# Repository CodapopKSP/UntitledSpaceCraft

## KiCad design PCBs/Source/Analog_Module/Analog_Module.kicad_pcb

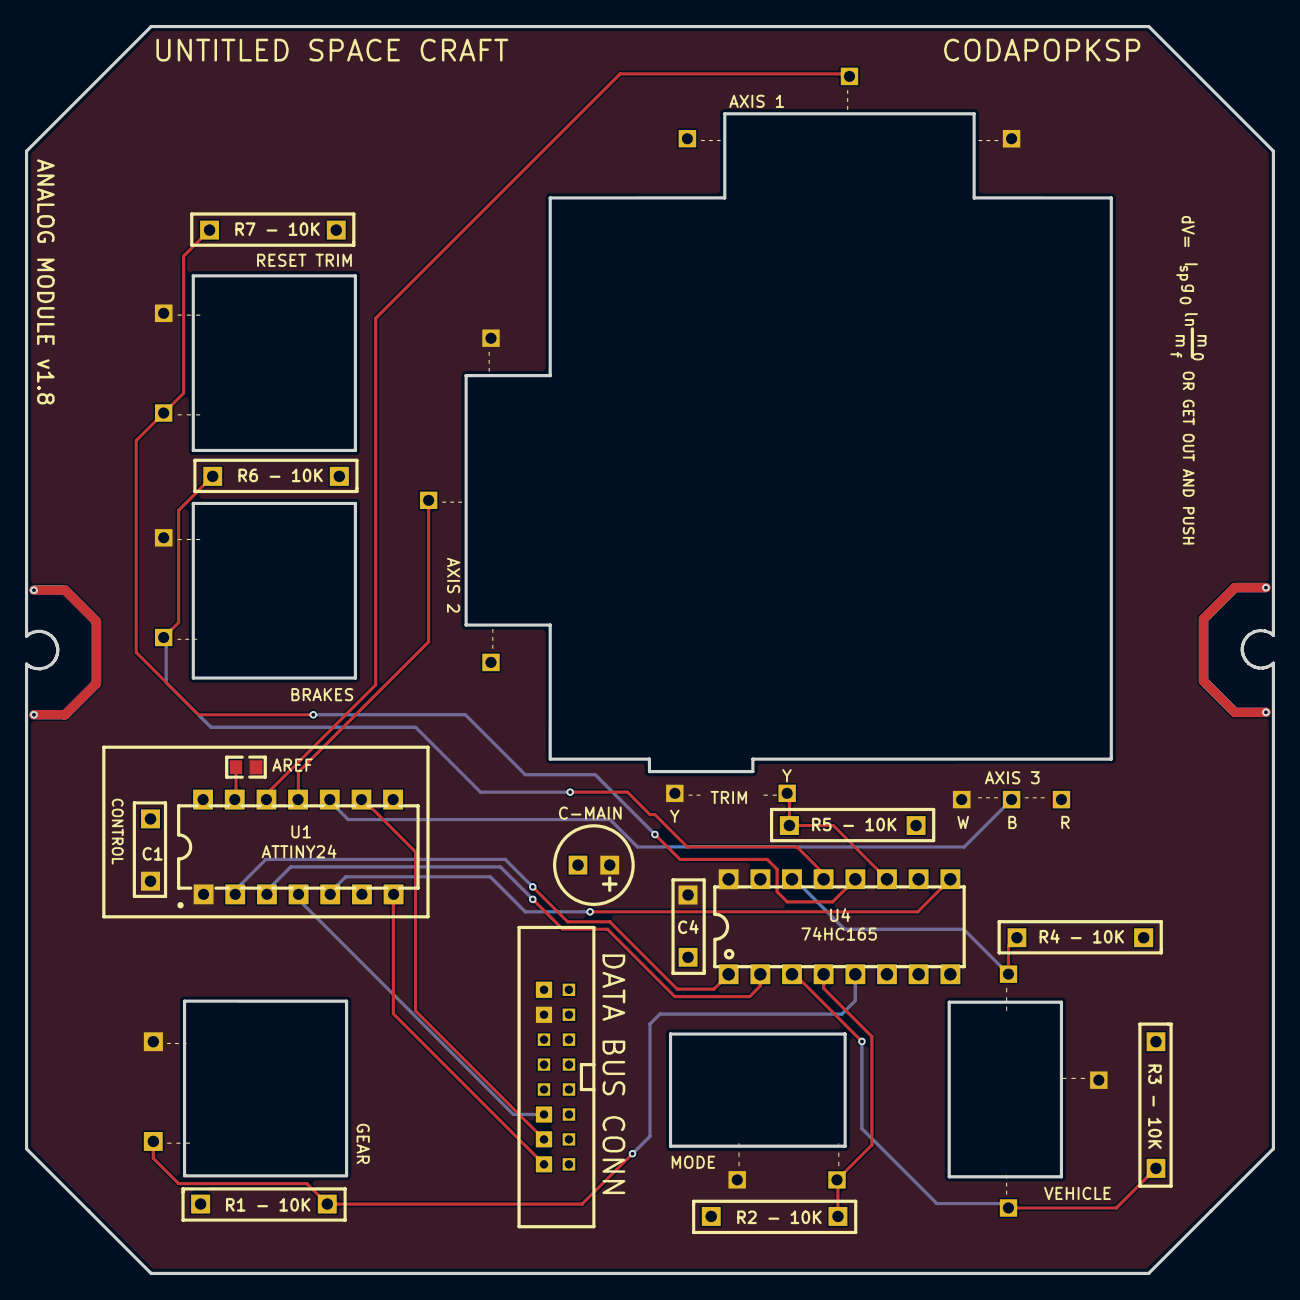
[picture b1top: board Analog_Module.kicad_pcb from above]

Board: 2 copper layers, 100.0 x 100.0 mm, 64 parts (0 on the bottom side), 19 nets.

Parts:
AREF: 10k; R0603
C1, C4: C104; TH_CAP_5mm
C-MAIN: 10uf; CAP-D6.3×F2.5
R1, R2, R3, R4, R5, R6, R7: - 10K; TH_RES_10mm
TP_+5V, TP_+5V#2, TP_+5V#3, TP_+5V#4, TP_+5V#5, TP_+5V#6, TP_+5V#7, TP_+5V#8, TP_+5V#9, TP_+5V#10: WirePad
TP_AREF: WirePad
TP_AXIS1, TP_AXIS1#2, TP_AXIS2, TP_AXIS2#2, TP_AXIS3, TP_AXIS3#2: WirePad
TP_BRAKES: WirePad
TP_CLOCK_Y_: WirePad
TP_CRUISE: WirePad
TP_DATA_P_: WirePad
TP_GEAR: WirePad
TP_GND: WirePad
TP_GND#2, TP_GND#3, TP_GND#4: WirePad
TP_LATCH_G_: WirePad
TP_MODE1, TP_MODE2: WirePad
TP_RESET: WirePad
TP_RESETTRIM: WirePad
TP_SCL: WirePad
TP_SDA: WirePad
TP_THROTTLE: WirePad
TP_TRANS: WirePad
TP_TRIM: WirePad
U4: 74HC165; DIP-16_L20.0-W6.4-P2.54-LS7.6-BL
WP11, WP24, WP25, WP38, WP39, WP43, WP44, WP45, WP46, WP47, WP48, WP49, WP50, WP51, WP52, WP53: WPAD-1-30AWG; WPAD-1-PTH-30AWG

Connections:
+5V: AREF.2, C1.2, C4.2, C-MAIN.1, TP_+5V.1, TP_+5V#2.1, TP_+5V#3.1, TP_+5V#4.1, TP_+5V#5.1, TP_+5V#6.1, TP_+5V#7.1, TP_+5V#8.1, TP_+5V#9.1, TP_+5V#10.1, U4.16, WP46.1
AREF: AREF.1, TP_AREF.13
AXIS1: TP_AXIS1.1, TP_AXIS1#2.12
AXIS2: TP_AXIS2.11, TP_AXIS2#2.1
AXIS3: TP_AXIS3.1, TP_AXIS3#2.10
BRAKES: R6.2, TP_BRAKES.1, U4.13
CLOCK(Y): TP_CLOCK_Y_.3, U4.2
DATA(P): TP_DATA_P_.5, U4.9
GEAR: R1.2, TP_GEAR.1, U4.5
GND: C1.1, C4.1, C-MAIN.2, R1.1, R2.1, R3.1, R4.1, R5.1, R6.1, R7.1, TP_GND.14, TP_GND#2.1, TP_GND#3.1, TP_GND#4.1, U4.6, U4.8, U4.15, WP45.1
LATCH(G): TP_LATCH_G_.2, U4.1
MODE1: R4.2, TP_MODE1.1, U4.14
MODE2: R3.2, TP_MODE2.1, U4.3
RESET: TP_RESET.4, WP50.1
RESETTRIM: R7.2, TP_RESETTRIM.1, U4.12
SCL: TP_SCL.9, WP51.1
SDA: TP_SDA.7, WP52.1
TRANS: R2.2, TP_TRANS.1, U4.4
TRIM: R5.2, TP_TRIM.1, U4.11

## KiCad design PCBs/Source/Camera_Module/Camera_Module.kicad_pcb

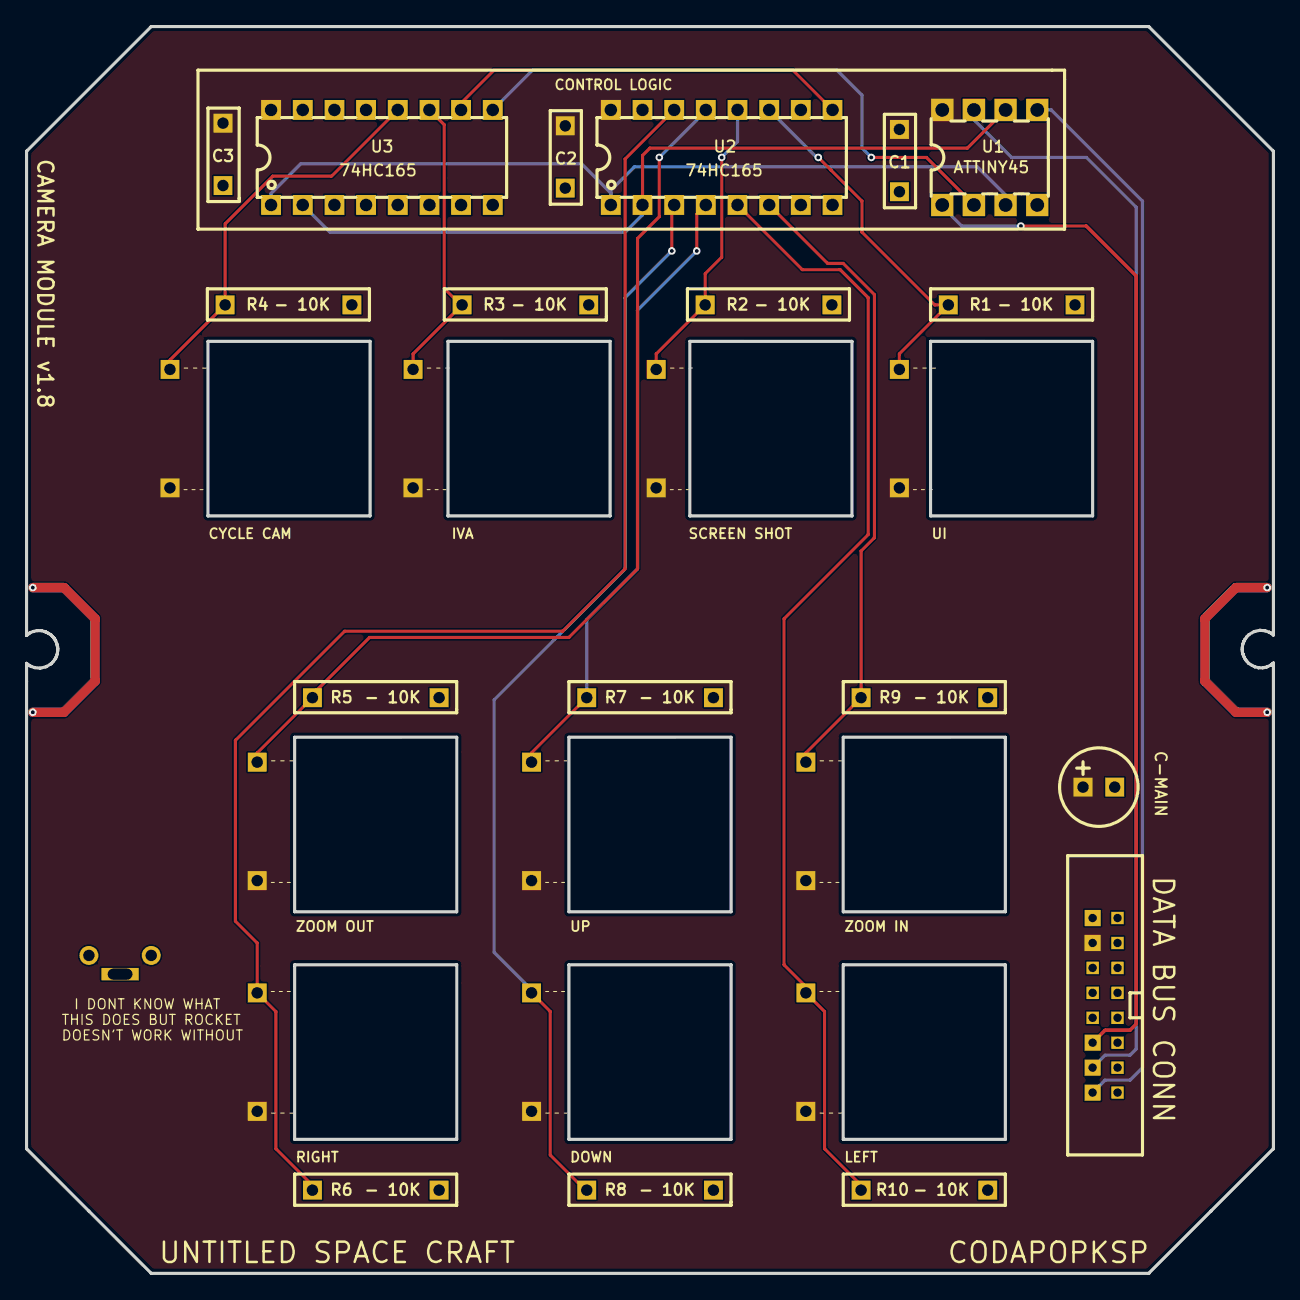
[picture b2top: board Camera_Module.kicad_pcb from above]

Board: 2 copper layers, 100.0 x 100.0 mm, 56 parts (0 on the bottom side), 19 nets.

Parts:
C1, C2, C3: C104; TH_CAP_5mm
C-MAIN: 10uf; CAP-D6.3×F2.5
R1, R2, R3, R4, R5, R6, R7, R8, R9, R10: - 10K; TH_RES_10mm
TP_+5V, TP_+5V#2, TP_+5V#3, TP_+5V#4, TP_+5V#5, TP_+5V#6, TP_+5V#7, TP_+5V#8, TP_+5V#9, TP_+5V#10: WirePad
TP_Pad_gge40554, TP_Pad_gge44183, TP_Pad_gge44204: WirePad
TP_UI1, TP_UI2, TP_UI3, TP_UI4, TP_UI5, TP_UI6, TP_UI7, TP_UI8, TP_UI9, TP_UI10: WirePad
U1: ATtiny45; PDIP-8_L9.3-W6.4-P2.54-LS7.6-BL
U2, U3: 74HC165; DIP-16_L20.0-W6.4-P2.54-LS7.6-BL
WP1, WP2, WP3, WP4, WP5, WP6, WP7, WP8, WP9, WP10, WP11, WP12, WP13, WP14, WP15, WP16: WPAD-1-30AWG; WPAD-1-PTH-30AWG

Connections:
+5V: C1.2, C2.2, C3.2, C-MAIN.1, TP_+5V#2.22, TP_+5V#6.10, TP_+5V#7.12, U1.8, U2.16, U3.16, WP7.1
CLOCK(Y): U1.6, U2.2, U3.2
DATA(B): U2.9, U3.10
DATA(P): U1.2, U3.9
GND: C1.1, C2.1, C3.1, C-MAIN.2, R1.1, R2.1, R3.1, R4.1, R5.1, R6.1, R7.1, R8.1, R9.1, R10.1, U1.4, U2.8, U2.15, U3.3, U3.4, U3.5, U3.6, U3.8, U3.13, U3.14, U3.15, WP8.1
LATCH(G): U1.3, U2.1, U3.1
RESET: U1.1, WP3.1
SCL: U1.7, WP2.1
SDA: U1.5, WP1.1
UI1: R1.2, TP_UI1.9, U2.11
UI2: R2.2, TP_UI2.11, U2.12
UI3: R3.2, TP_UI3.13, U3.11
UI4: R4.2, TP_UI4.15, U3.12
UI5: R5.2, TP_UI5.17, U2.13
UI6: R6.2, TP_UI6.23, U2.14
UI7: R7.2, TP_UI7.19, U2.4
UI8: R8.2, TP_UI8.25, U2.3
UI9: R9.2, TP_UI9.21, U2.6
UI10: R10.2, TP_UI10.27, U2.5

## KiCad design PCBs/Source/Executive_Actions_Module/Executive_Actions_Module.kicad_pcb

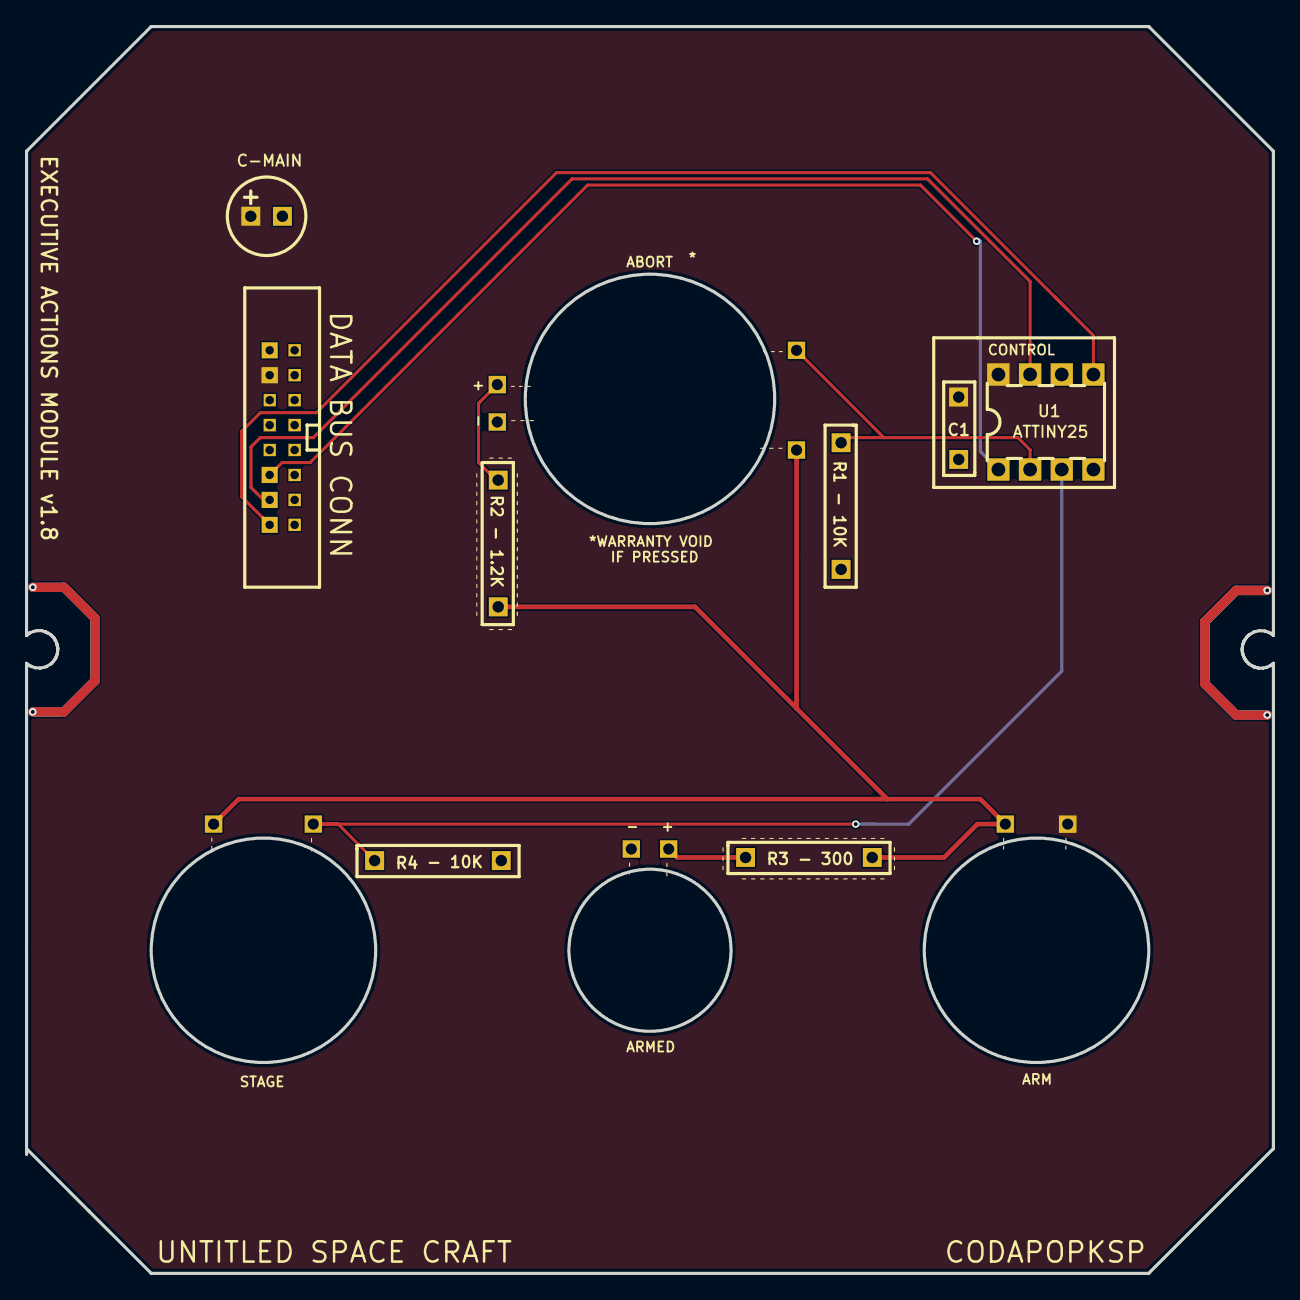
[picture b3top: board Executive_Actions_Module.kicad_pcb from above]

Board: 2 copper layers, 100.0 x 100.0 mm, 33 parts (0 on the bottom side), 10 nets.

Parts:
C1: C104; TH_CAP_5mm
C-MAIN: 10uf; CAP-D6.3×F2.5
R1, R4: - 10K; TH_RES_10mm
R2: - 1.2K; TH_RES_10mm
R3: - 300; TH_RES_10mm
TP_+5V: WirePad
TP_ABORT: WirePad
TP_ARMED: WirePad
TP_GND: WirePad
TP_GND#2: WirePad
TP_LIGHT, TP_LIGHT2: WirePad
TP_STAGE: WirePad
U1: ATtiny25; PDIP-8_L9.3-W6.4-P2.54-LS7.6-BL
WP1, WP2, WP3, WP4, WP5, WP6, WP7, WP8, WP9, WP10, WP11, WP12, WP13, WP14, WP15, WP16, WP82, WP83: WPAD-1-30AWG; WPAD-1-PTH-30AWG

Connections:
+5V: C1.2, C-MAIN.1, TP_+5V.1, U1.8, WP7.1
ABORT: R1.1, TP_ABORT.1, U1.2
ARMED: R2.2, R3.2, TP_ARMED.1, WP82.1, WP83.1
GND: C1.1, C-MAIN.2, R1.2, R4.2, TP_GND.1, TP_GND#2.1, U1.4, WP8.1
LIGHT: R3.1, TP_LIGHT.1
LIGHT2: R2.1, TP_LIGHT2.1
RESET: U1.1, WP3.1
SCL: U1.7, WP2.1
SDA: U1.5, WP1.1
STAGE: R4.1, TP_STAGE.1, U1.3

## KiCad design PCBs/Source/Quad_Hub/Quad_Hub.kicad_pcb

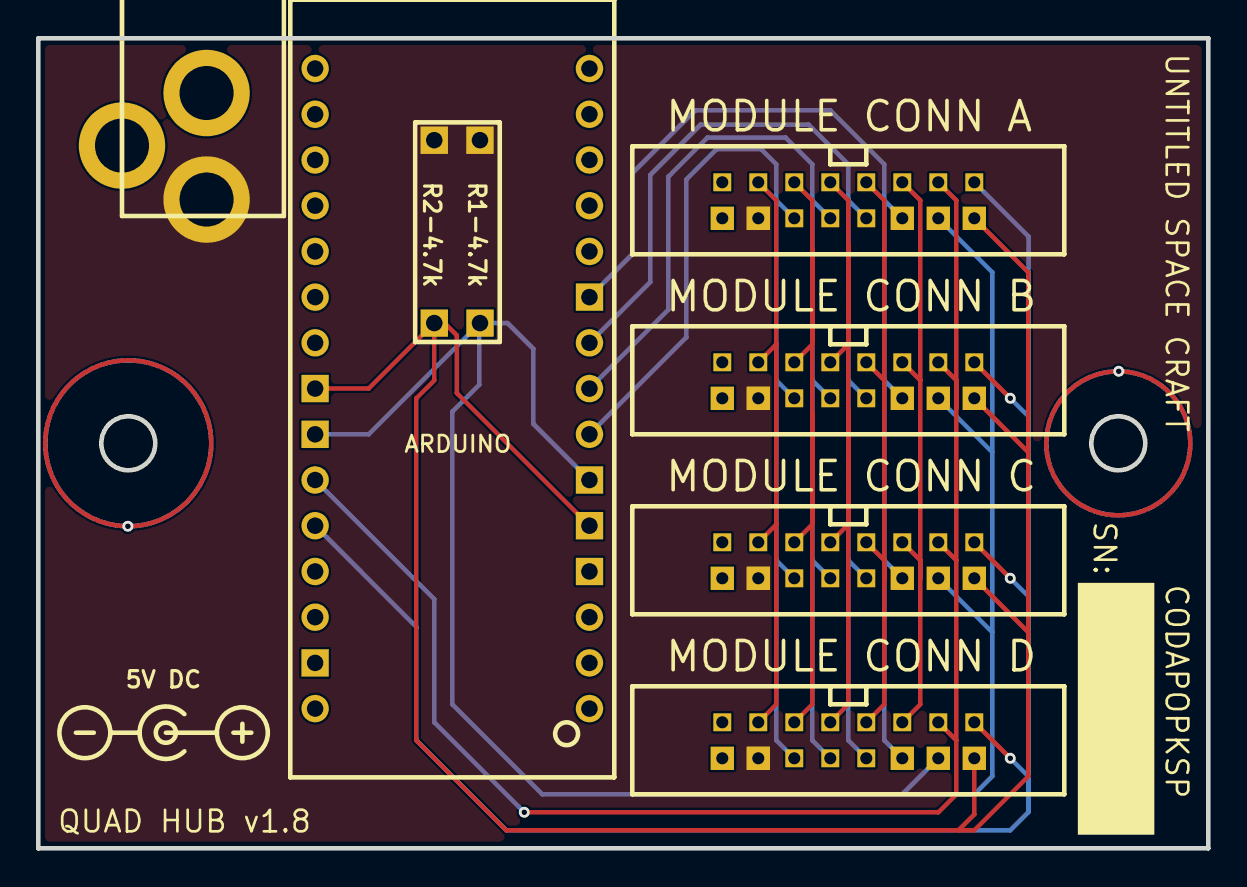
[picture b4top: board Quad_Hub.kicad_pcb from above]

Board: 2 copper layers, 65.0 x 45.0 mm, 68 parts (0 on the bottom side), 15 nets.

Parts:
ARDUINO: Arduino_Nano_Header; DIP-30_L43.18-W15.24-ARDUINONANO
NONE: _
NONEAWD: _
U1: PJ-102A
WP17, WP18, WP19, WP20, WP21, WP22, WP23, WP24, WP25, WP26, WP27, WP28, WP29, WP30, WP31, WP32, WP33, WP34, WP35, WP36, WP37, WP38, WP39, WP40, WP41, WP42, WP43, WP44, WP45, WP46, WP47, WP48, WP49, WP50, WP51, WP52, WP53, WP54, WP55, WP56, WP57, WP58, WP59, WP60, WP61, WP62, WP63, WP64, WP65, WP66, WP67, WP68, WP69, WP70, WP71, WP72, WP73, WP74, WP75, WP76, WP77, WP78, WP79, WP80: WPAD-1-30AWG; WPAD-1-PTH-30AWG

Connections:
+5V: NONE.2, NONE.4, U1.TIP, WP24.1, WP41.1, WP57.1, WP73.1
ANALOG0: WP20.1, WP45.1, WP61.1, WP77.1
ANALOG1: WP19.1, WP46.1, WP62.1, WP78.1
ANALOG2: WP18.1, WP47.1, WP63.1, WP79.1
ANALOG3: WP32.1, WP33.1, WP49.1, WP65.1
ANALOG4: ARDUINO.25, WP31.1, WP34.1, WP50.1, WP66.1
ANALOG5: ARDUINO.26, WP17.1, WP48.1, WP64.1, WP80.1
DIGITAL1: WP21.1, WP44.1, WP60.1, WP76.1
DIGITAL2: ARDUINO.7, WP25.1, WP40.1, WP56.1, WP72.1
DIGITAL3: ARDUINO.8, WP26.1, WP39.1, WP55.1, WP71.1
DIGITAL4: ARDUINO.9, WP27.1, WP38.1, WP54.1, WP70.1
GND: ARDUINO.4, ARDUINO.29, U1.RING, WP23.1, WP42.1, WP58.1, WP74.1
RESET: ARDUINO.10, WP28.1, WP37.1, WP53.1, WP69.1
SCL: ARDUINO.6, ARDUINO.24, NONE.5, WP29.1, WP36.1, WP52.1, WP68.1
SDA: ARDUINO.5, ARDUINO.23, NONE.3, WP30.1, WP35.1, WP51.1, WP67.1
